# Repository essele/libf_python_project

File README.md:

# libf_python_project
LIBF MSc Computer Science -- Python Programming Project

An object oriented Python system to take a KiCAD PCB and export
suitable files for use with PCBA capabilities from JLCPCB

# Quick testing (assuming a Linux system, with KiCad installed)

1. Download the code from GitHub
2. cd into the libf_python_project/plugin directory
3. Run: ./libf_plugin.py ../sample/sample_board.kicad_pcb
4. cd back into the main directory: cd ..
5. Run: ./process_files.py sample
6. out_bom.csv and out_cpl.csv will be created in this directory

# Plugin

The plugin can be installed in KiCad by copying or linking the plugin directory 
to your kicad scripting/plugins directory.

When you restart (or refresh the plugins) you will see a button with the L from
the LIFB logo on the toolbar. This will execute the plugin against the current
PCB.

Alternatively you can execute the plugin from the command-line if you provide
a suitable .kicad_pcb file to run against.

The board.csv and components.csv files will be created in the same directory as
the board file.

# Main Processing

The main script can be executed without KiCad being installed and can use the
sample board.csv and component.csv files included with this archive.

Usage: ./process_files.py <directory_with_csv_files_in>

So to use the sample board, you can use the following:

./process_files.py ./sample

This will produce an out_bom.csv and an out_cpl.csv file in the current directory.

# License

Please note that this project is not currently open-source as it was built
for a specific University need. A future version may be made available that
will be open-source.

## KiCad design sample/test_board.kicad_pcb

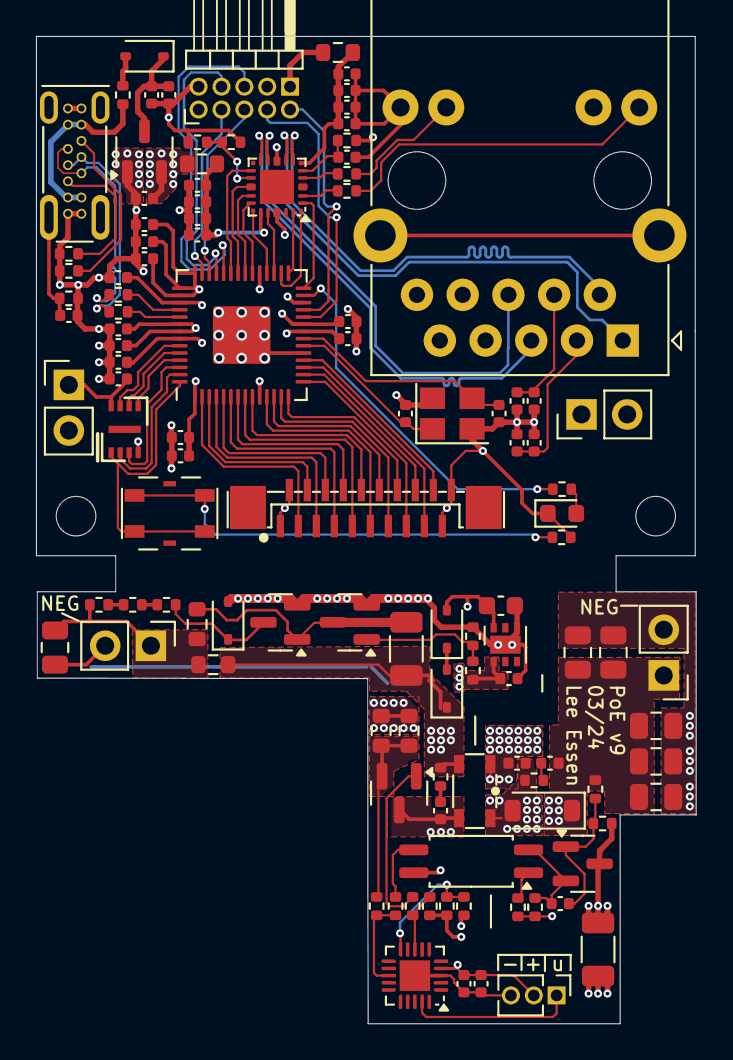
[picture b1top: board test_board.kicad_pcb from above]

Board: 4 copper layers, 36.7 x 54.8 mm, 112 parts (0 on the bottom side), 98 nets.

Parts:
C1, C3, C5, C10, C100, C102, C105, C106, C108, C110, C112, C118, C119, C121, C122, C123: 0.1uF; C_0402_1005Metric
C2, C4, C6, C11, C101, C103, C104, C107: 1uF; C_0402_1005Metric
C7, C9, C109, C204: 10n; C_0402_1005Metric
C8, C12: 4.7u; C_0402_1005Metric
C117, C125: 33pF; C_0402_1005Metric
C201: 1u; C_0603_1608Metric
C202: 10u; C_0402_1005Metric
C203: 100n; C_0805_2012Metric
C205: 100n; C_0402_1005Metric
C206: 1u; C_1206_3216Metric
C207: 100p; C_0402_1005Metric
C208: 1nF; C_1206_3216Metric
C209: 220pF; C_0402_1005Metric
C210: 1nF; C_0402_1005Metric
C211: 10u 25V; C_0805_2012Metric
C212, C213, C214, C216: 22uF; C_0805_2012Metric
C215: 4.7n; C_0402_1005Metric
D100: 1N5819WS; D_SOD-323
D101: BLUE; LED_0603_1608Metric
D201, D202, D203: 5V6; D_SOD-323
D204: B5819W; D_SOD-123
F100: 200mA; R_0402_1005Metric
FB1, FB2: FerriteBead; R_0603_1608Metric
FB201: 600R @ 100MHz; R_0603_1608Metric
J1: Conn_01x20_Male; FPC_0.5K-A-20PBv2
J100: POE_3V3; PinHeader_1x02_P2.54mm_Vertical_JLCPCB
J101: USB_C_Receptacle_USB2.0; USB_C_LCSC_C428464_SIDE
J103: POE_IN; PinHeader_1x02_P2.54mm_Vertical_JLCPCB
J104: RJ45_Wurth_7499210121A
J106: DEBUG; PinHeader_2x05_X1321WR-2x05J
J201, J202: Conn_01x02_Male; PinHeader_1x02_P2.54mm_Vertical
J203: DEBUG; PinHeader_1x03_P1.27mm_Vertical
Q201, Q202, Q203: AS2324; SOT-23
R1, R2, R219: 12K; R_0402_1005Metric
R3, R133, R217: 1K; R_0402_1005Metric
R100, R103: 5.1k; R_0402_1005Metric
R101, R201, R207, R213: 1M; R_0402_1005Metric
R102, R111, R113: 470; R_0402_1005Metric
R104, R108: 22; R_0402_1005Metric
R105: 6.8K; R_0402_1005Metric
R106: 150k; R_0402_1005Metric
R110: 4k7; R_0402_1005Metric
R202: 2M; R_0603_1608Metric
R205, R206: 49.9; R_0402_1005Metric
R208, R210: 4.7R; R_0603_1608Metric
R209: 100R; R_0402_1005Metric
R211: 3.3K; R_0402_1005Metric
R212: 10R; R_0402_1005Metric
R214: 51k; R_0402_1005Metric
R215: 4K7; R_0402_1005Metric
R216: 510; R_0402_1005Metric
R218: 20K; R_0402_1005Metric
SW1: SW_Push; SW_SPST_ C2888419
T201: ATB322524-0110-T000; TDK_ATB
U100: XC6206PxxxMR; SOT-23-3
U101: DP83825I; WQFN24-DP83825I
U102: RP2040; RP2040-QFN-56
U103: ZD25WQ16; 8-uson-v2
U201: AP7387-3.3_UDFN2020-6; Diodes_UDFN2020-6_Type-C
U202: ATtiny1616-M; VQFN-20-1EP_3x3mm_P0.4mm_EP1.7x1.7mm
U203: EL3H7(B); SOP-4_4.4x2.6mm_P1.27mm
U204: AZ432; SOT-23
Y100: 12MHz; Crystal_SMD_3225-4Pin_3.2x2.5mm

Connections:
/+3V3: C100.2, C102.2, C103.2, C104.2, C105.2, C106.2, C118.2, C119.2, C121.2, C122.2, FB1.1, FB2.1, J100.1, J106.1, R110.1, U100.2 (VO), U102.1 (IOVDD), U102.10 (IOVDD), U102.22 (IOVDD), U102.26 (RUN), U102.33 (IOVDD), U102.42 (IOVDD), U102.43 (ADC_AVDD), U102.44 (VREG_IN), U102.48 (USB_VDD), U102.49 (IOVDD), U103.8 (VCC)
/+5V: C107.2, C108.2, D100.1 (K), U100.3 (VI)
/+P3V3: C210.1, C211.1, C212.1, C213.1, C214.1, C216.1, D204.1 (K), J202.1, R216.2, R217.1, R218.1
/ATN: J1.18, U102.18 (GPIO15)
/CRS: U101.20 (CRS_DV), U102.31 (GPIO20)
/DAV: J1.13, U102.13 (GPIO10)
/DIO1: J1.3, U102.2 (GPIO0)
/DIO2: J1.4, U102.3 (GPIO1)
/DIO3: J1.5, U102.4 (GPIO2)
/DIO4: J1.6, U102.5 (GPIO3)
/DIO5: J1.7, U102.6 (GPIO4)
/DIO6: J1.8, U102.7 (GPIO5)
/DIO7: J1.9, U102.8 (GPIO6)
/DIO8: J1.10, U102.9 (GPIO7)
/DVDD: C101.2, C110.2, C123.2, U102.23 (DVDD), U102.45 (VREG_VOUT), U102.50 (DVDD)
/EOI: J1.11, U102.11 (GPIO8)
/ETH_VDD: C9.2, C10.2, C11.2, C12.2, FB2.2, U101.6 (VDDA3V3)
/ETH_VDDIO: C5.2, C6.2, C7.2, C8.2, FB1.2, U101.19 (VDDIO)
/FB: R211.2, R215.1, U202.13 (PB1)
/Gate: R206.2, R207.1, U202.8 (PA7)
/I2C_SCL: J106.7, U102.39 (GPIO27_ADC1)
/I2C_SDA: J106.5, U102.38 (GPIO26_ADC0)
/IFC: J1.16, U102.16 (GPIO13)
/INH: Q201.1 (G), R201.1, R205.1
/LED1: R102.2, U102.27 (GPIO16)
/LLED: R111.2, U101.2 (LED2/50MO)
/MDC: U101.16 (MDC), U102.35 (GPIO23)
/MDIO: U101.15 (MDIO), U102.36 (GPIO24)
/NDAC: J1.15, U102.15 (GPIO12)
/NRFD: J1.14, U102.14 (GPIO11)
/PGND: C208.2, C209.2, C211.2, C212.2, C213.2, C214.2, C216.2, J202.2, R219.2, T201.6, U204.3 (A)
/PHYCLK: U101.13 (XI/50MI), U102.37 (GPIO25)
/POE+: C203.1, FB201.1, J201.1, R1.1, R202.1
/POE-: C201.2, C202.2, C203.2, C204.2, C205.2, C208.1, D201.2 (A), J201.2, J203.3, Q201.2 (S), Q202.2 (S), R201.2, R207.2, R208.2, R210.2, R214.2, U201.4 (GND), U201.7 (GND), U202.3 (GND), U202.21 (GND)
/POS: C206.1, D202.1 (K), FB201.2, R209.1, T201.1
/QSPI_SCLK: U102.52 (QSPI_SCLK), U103.6 (CLK)
/QSPI_SD0: U102.53 (QSPI_SD0), U103.5 (DI(IO0))
/QSPI_SD1: U102.55 (QSPI_SD1), U103.2 (DO(IO1))
/QSPI_SD2: U102.54 (QSPI_SD2), U103.3 (IO2)
/QSPI_SD3: U102.51 (QSPI_SD3), U103.7 (IO3)
/QSPI_SS: SW1.2, U102.56 (QSPI_SS), U103.1 (~CS)
/RD_N: J104.2 (RD-), U101.7 (RD_M)
/RD_P: J104.1 (RD+), U101.8 (RD_P)
/REN: J1.12, U102.12 (GPIO9)
/RLED: R113.2, U101.4 (LED0)
/RXD0: U101.18 (RXD0), U102.32 (GPIO21)
/RXD1: U101.17 (RXD1), U102.34 (GPIO22)
/SRQ: J1.17, U102.17 (GPIO14)
/SWCLK: J106.4, U102.24 (SWCLK)
/SWD: J106.2, U102.25 (SWD)
/TD_N: J104.6 (TD-), U101.10 (TD_M)
/TD_P: J104.5 (TD+), U101.11 (TD_P)
/TXD0: U101.23 (TXD0), U102.29 (GPIO18)
/TXD1: U101.24 (TXD1), U102.30 (GPIO19)
/TXEN: U101.1 (TXEN), U102.28 (GPIO17)
/UART_RX: J106.8, U102.41 (GPIO29_ADC3)
/UART_TX: J106.6, U102.40 (GPIO28_ADC2)
/UPDI: J203.1, U202.19 (~RESET/PA0)
/USBD_N: J101.A7 (D-), J101.B7 (D-), R104.1
/USBD_P: J101.A6 (D+), J101.B6 (D+), R108.1
/USB_DM: R104.2, U102.46 (USB_DM)
/USB_DP: R108.2, U102.47 (USB_DP)
/VREG: C201.1, D203.2 (A), R213.1, U201.6 (VI)
/Vmcu: C202.1, C204.1, C205.1, J203.2, R205.2, U201.1 (VO), U202.4 (VCC), U203.4
/XPOE+: J103.1, J104.9 (V+)
/XPOE-: J103.2, J104.10 (V-)
GND: C1.1, C2.1, C3.1, C4.1, C5.1, C6.1, C7.1, C8.1, C9.1, C10.1, C11.1, C12.1, C100.1, C101.1, C102.1, C103.1, C104.1, C105.1, C106.1, C107.1, C108.1, C109.1, C110.1, C112.1, C117.1, C118.1, C119.1, C121.1, C122.1, C123.1, C125.1, D101.1 (K), J1.1, J1.2, J1.19, J1.20, J100.2, J101.A1 (GND), J101.A12 (GND), J101.B1 (GND), J101.B12 (GND), J104.7, J104.12 (LLED-), J104.14 (RLED-), J106.3, J106.9, R100.2, R101.2, R103.2, R105.2, R106.2, R133.2, U100.1 (GND), U101.9 (GND), U101.21 (GND), U102.19 (TESTEN), U102.57 (GND), U103.4 (GND), Y100.2, Y100.4
unnamed: C1.2, C2.2, J104.3 (CT)
unnamed: C3.2, C4.2, J104.4 (CT)
unnamed: C109.2, J101.17 (SHIELD), J101.18 (SHIELD), J101.19 (SHIELD), J101.20 (SHIELD), R101.1
unnamed: C207.1, R209.2
unnamed: C210.2, R212.1
unnamed: D100.2 (A), F100.1
unnamed: D101.2 (A), R102.1
unnamed: D201.1 (K), Q202.3 (D), R3.2
unnamed: D202.2 (A), D203.1 (K)
unnamed: C209.1, D204.2 (A), R212.2, T201.5
unnamed: F100.2, J101.A4 (VBUS), J101.A9 (VBUS), J101.B4 (VBUS), J101.B9 (VBUS)
unnamed: J101.A5 (CC1), R103.1
unnamed: J101.B5 (CC2), R100.1
unnamed: J104.11 (LLED+), R111.1
unnamed: J104.13 (RLED+), R113.1
unnamed: C206.2, Q201.3 (D), Q202.1 (G), R202.2
unnamed: C207.2, Q203.3 (D), T201.2
unnamed: Q203.1 (G), R206.1
unnamed: Q203.2 (S), R208.1, R210.1, R211.1
unnamed: R1.2, R2.1
unnamed: R2.2, R3.1
unnamed: R133.1, SW1.1
unnamed: R215.2, U203.3
unnamed: R216.1, U203.1
unnamed: R105.1, R106.1, U101.14 (RBIAS)
unnamed: C112.2, R110.2, U101.5 (~RST)
unnamed: C117.2, U102.20 (XIN), Y100.1
unnamed: C125.2, U102.21 (XOUT), Y100.3
unnamed: R213.2, R214.1, U202.10 (PB4)
unnamed: C215.1, R217.2, U203.2, U204.2 (K)
unnamed: C215.2, R218.2, R219.1, U204.1 (REF)

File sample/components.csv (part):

ref,value,layer,footprint,lcsc,x,y,rot,top,left,bottom,right
C122,0.1uF,F.Cu,C_0402_1005Metric,C1525,142750000,114950000,0.0,114440001,141790001,115459999,143709999
C100,0.1uF,F.Cu,C_0402_1005Metric,C1525,139300000,108825000,0.0,108315001,138340001,109334999,140259999
C101,1uF,F.Cu,C_0402_1005Metric,C52923,139300000,105050000,0.0,104540001,138340001,105559999,140259999
C102,0.1uF,F.Cu,C_0402_1005Metric,C1525,140750000,103050000,0.0,102540001,139790001,103559999,141709999
C103,1uF,F.Cu,C_0402_1005Metric,C52923,140750000,104000000,0.0,103490001,139790001,104509999,141709999
U103,ZD25WQ16,F.Cu,8-uson-v2,C2983691,139650000,113475000,90.0,111675001,138350001,115274999,140949999
R1,12K,F.Cu,R_0402_1005Metric,C25752,138225000,123225000,0.0,122705001,137245001,123744999,139204999
D203,5V6,F.Cu,D_SOD-323,C2832598,157550000,124575000,90.0,122925001,156550001,126224999,158549999
R213,1M,F.Cu,R_0402_1005Metric,C26083,158500000,139965000,90.0,138985001,157980001,140944999,159019999
C209,220pF,F.Cu,C_0402_1005Metric,C1530,161450000,132025000,180.0,131515001,160490001,132534999,162409999
R111,470,F.Cu,R_0402_1005Metric,C25117,152000000,100230000,180.0,99710001,151020001,100749999,152979999
R216,510,F.Cu,R_0402_1005Metric,C25123,161500000,140025000,-90.0,139045001,160980001,141004999,162019999
D100,1N5819WS,F.Cu,D_SOD-323,C191023,140755000,92750000,180.0,91750001,139105001,93749999,142404999
Q201,AS2324,F.Cu,SOT-23,C232272,152162500,124200000,180.0,122450001,150192501,125949999,154132499
C119,0.1uF,F.Cu,C_0402_1005Metric,C1525,152050000,108440000,180.0,107930001,151090001,108949999,153009999
D202,5V6,F.Cu,D_SOD-323,C2832598,157550000,127875000,90.0,126225001,156550001,129524999,158549999
C2,1uF,F.Cu,C_0402_1005Metric,C52923,161450000,114225000,-90.0,113265001,160940001,115184999,161959999
U101,DP83825I,F.Cu,WQFN24-DP83825I,C783599,148112500,100010000,180.0,98185001,146287501,101834999,149937499
C117,33pF,F.Cu,C_0402_1005Metric,C1562,155250000,112600000,-90.0,111640001,154740001,113559999,155759999
FB1,FerriteBead,F.Cu,R_0603_1608Metric,C1002,143950000,98730000,0.0,97950001,142420001,99509999,145479999
J101,USB_C_Receptacle_USB2.0,F.Cu,USB_C_LCSC_C428464_SIDE,C428464,136875000,98700000,0.0,88350001,134725001,103299999,139024999
C12,4.7u,F.Cu,C_0402_1005Metric,C23733,152000000,93730000,180.0,93220001,151040001,94239999,152959999
C212,22uF,F.Cu,C_0805_2012Metric,C16780,169175000,131925000,0.0,130895001,167425001,132954999,170924999
R210,4.7R,F.Cu,R_0603_1608Metric,C23164,155450000,130225000,90.0,128695001,154670001,131754999,156229999
R105,6.8K,F.Cu,R_0402_1005Metric,C25917,145575000,97525000,0.0,97005001,144595001,98044999,146554999
R104,22,F.Cu,R_0402_1005Metric,C25092,139300000,106000000,0.0,105480001,138320001,106519999,140279999
U202,ATtiny1616-M,F.Cu,VQFN-20-1EP_3x3mm_P0.4mm_EP1.7x1.7mm,C507118,155775000,143825000,180.0,141675001,153625001,145974999,157924999
R208,4.7R,F.Cu,R_0603_1608Metric,C23164,153900000,130225000,90.0,128695001,153120001,131754999,154679999
C213,22uF,F.Cu,C_0805_2012Metric,C16780,169175000,133900000,0.0,132870001,167425001,134929999,170924999
D101,BLUE,F.Cu,LED_0603_1608Metric,C2986058,163950000,118150000,0.0,117370001,162420001,118929999,165479999
R103,5.1k,F.Cu,R_0402_1005Metric,C25905,136550000,104675000,180.0,104155001,135570001,105194999,137529999
U100,XC6206PxxxMR,F.Cu,SOT-23-3,C5446,140750000,98050000,90.0,95950001,139000001,100149999,142499999
Q202,AS2324,F.Cu,SOT-23,C232272,148300000,124200000,180.0,122450001,146330001,125949999,150269999
C203,100n,F.Cu,C_0805_2012Metric,C28233,135780000,125600000,-90.0,123850001,134750001,127349999,136809999
C112,0.1uF,F.Cu,C_0402_1005Metric,C1525,152000000,98360000,180.0,97850001,151040001,98869999,152959999
C110,0.1uF,F.Cu,C_0402_1005Metric,C1525,139300000,109750000,0.0,109240001,138340001,110259999,140259999
C8,4.7u,F.Cu,C_0402_1005Metric,C23733,143700000,102680000,0.0,102170001,142740001,103189999,144659999
C109,10n,F.Cu,C_0402_1005Metric,C15195,136550000,107150000,180.0,106640001,135590001,107659999,137509999
C208,1nF,F.Cu,C_1206_3216Metric,C9196,165950000,142375000,90.0,140025001,164750001,144724999,167149999
C202,10u,F.Cu,C_0402_1005Metric,C15525,161000000,127325000,0.0,126815001,160040001,127834999,161959999
J104,RJ45_Wurth_7499210121A,F.Cu,RJ45_Wurth_7499210121A,C22365442,167320000,108545000,180.0,88205001,151810001,110894999,171409999
C215,4.7n,F.Cu,C_0402_1005Metric,C1538,163850000,139825000,0.0,139315001,162890001,140334999,164809999
R101,1M,F.Cu,R_0402_1005Metric,C26083,136550000,106200000,0.0,105680001,135570001,106719999,137529999
R209,100R,F.Cu,R_0402_1005Metric,C25076,157200000,132785000,-90.0,131805001,156680001,133764999,157719999
Q203,AS2324,F.Cu,SOT-23,C232272,154900000,133687500,-90.0,131717501,153150001,135657499,156649999
U204,AZ432,F.Cu,SOT-23,C84139,165100000,137612500,0.0,135862501,163130001,139362499,167069999
R214,51k,F.Cu,R_0402_1005Metric,C25794,157550000,139965000,-90.0,138985001,157030001,140944999,158069999
C108,0.1uF,F.Cu,C_0402_1005Metric,C1525,141150000,94900000,90.0,93940001,140640001,95859999,141659999
C10,0.1uF,F.Cu,C_0402_1005Metric,C1525,152000000,95580000,180.0,95070001,151040001,96089999,152959999
R3,1K,F.Cu,R_0402_1005Metric,C11702,141975000,123225000,0.0,122705001,140995001,123744999,142954999
R2,12K,F.Cu,R_0402_1005Metric,C25752,140100000,123225000,0.0,122705001,139120001,123744999,141079999
C107,1uF,F.Cu,C_0402_1005Metric,C52923,142100000,94900000,90.0,93940001,141590001,95859999,142609999
R215,4K7,F.Cu,R_0402_1005Metric,C25900,154700000,139965000,90.0,138985001,154180001,140944999,155219999
C118,0.1uF,F.Cu,C_0402_1005Metric,C1525,142750000,113930000,0.0,113420001,141790001,114439999,143709999
J1,Conn_01x20_Male,F.Cu,FPC_0.5K-A-20PBv2,C11073,153050000,117850000,0.0,115900001,145150001,119824999,160949999
R212,10R,F.Cu,R_0402_1005Metric,C25077,162400000,132975000,180.0,132455001,161420001,133494999,163379999
C106,0.1uF,F.Cu,C_0402_1005Metric,C1525,139300000,107900000,0.0,107390001,138340001,108409999,140259999
C207,100p,F.Cu,C_0402_1005Metric,C343055,157200000,134660000,-90.0,133700001,156690001,135619999,157709999
C11,1uF,F.Cu,C_0402_1005Metric,C52923,152000000,94650000,180.0,94140001,151040001,95159999,152959999
FB201,600R @ 100MHz,F.Cu,R_0603_1608Metric,C1002,144575000,126550000,0.0,125770001,143045001,127329999,146104999
C201,1u,F.Cu,C_0603_1608Metric,C15849,160550000,123275000,0.0,122495001,159020001,124054999,162079999
Y100,12MHz,F.Cu,Crystal_SMD_3225-4Pin_3.2x2.5mm,C9002,157850000,112600000,0.0,110850001,155700001,114349999,159999999
J106,DEBUG,F.Cu,PinHeader_2x05_X1321WR-2x05J,C2881825,146300000,95075000,180.0,88090001,142560001,96689999,150059999
C7,10n,F.Cu,C_0402_1005Metric,C15195,143700000,101760000,0.0,101250001,142740001,102269999,144659999
C105,0.1uF,F.Cu,C_0402_1005Metric,C1525,139300000,110675000,0.0,110165001,138340001,111184999,140259999
R102,470,F.Cu,R_0402_1005Metric,C25117,163950000,116800000,180.0,116280001,162970001,117319999,164929999
C1,0.1uF,F.Cu,C_0402_1005Metric,C1525,162400000,114225000,-90.0,113265001,161890001,115184999,162909999
R202,2M,F.Cu,R_0603_1608Metric,C22976,143675000,124300000,90.0,122770001,142895001,125829999,144454999
C214,22uF,F.Cu,C_0805_2012Metric,C16780,166800000,125875000,90.0,124125001,165770001,127624999,167829999
C204,10n,F.Cu,C_0402_1005Metric,C15195,159450000,144275000,-90.0,143315001,158940001,145234999,159959999
C211,10u 25V,F.Cu,C_0805_2012Metric,C15850,164825000,125875000,90.0,124125001,163795001,127624999,165854999
D204,B5819W,F.Cu,D_SOD-123,C8598,162850000,134660000,180.0,133460001,160450001,135859999,165249999
J103,POE_IN,F.Cu,PinHeader_1x02_P2.54mm_Vertical_JLCPCB,C358684,166300000,112650000,0.0,110800001,163180001,114499999,169429999
C4,1uF,F.Cu,C_0402_1005Metric,C52923,161450000,111900000,90.0,110940001,160940001,112859999,161959999
R133,1K,F.Cu,R_0402_1005Metric,C11702,163925000,119475000,0.0,118955001,162945001,119994999,164904999
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
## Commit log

2024-08-14 Testing comit
2024-08-14 initial commit of plugin part
2024-08-15 experiments with drawing a board in bokeh
2024-08-15 more efficient drawing
2024-08-16 major tidy, plus start of BOM work
2024-08-16 added csv file generation
2024-08-16 added support for rotations
2024-08-18 moved rotdb into an object
2024-08-18 more tidy/commenting + bar chart
2024-08-19 more tidying and a bug fix
2024-08-19 added unit tests
2024-08-20 added Component unit test
2024-08-21 cleanup and getBOMKey improvement
2024-08-21 tidy and comment
2024-08-21 added sample board
